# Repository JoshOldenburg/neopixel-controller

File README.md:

Neopixel Controllers
====================

Various Neopixel-style LED strip controllers based on the ATtiny85 microcontroller. Due to their size these aren't capable of more than 1A or so, preferably much less. The `neopixel-controller` files are for a standalone controller board.

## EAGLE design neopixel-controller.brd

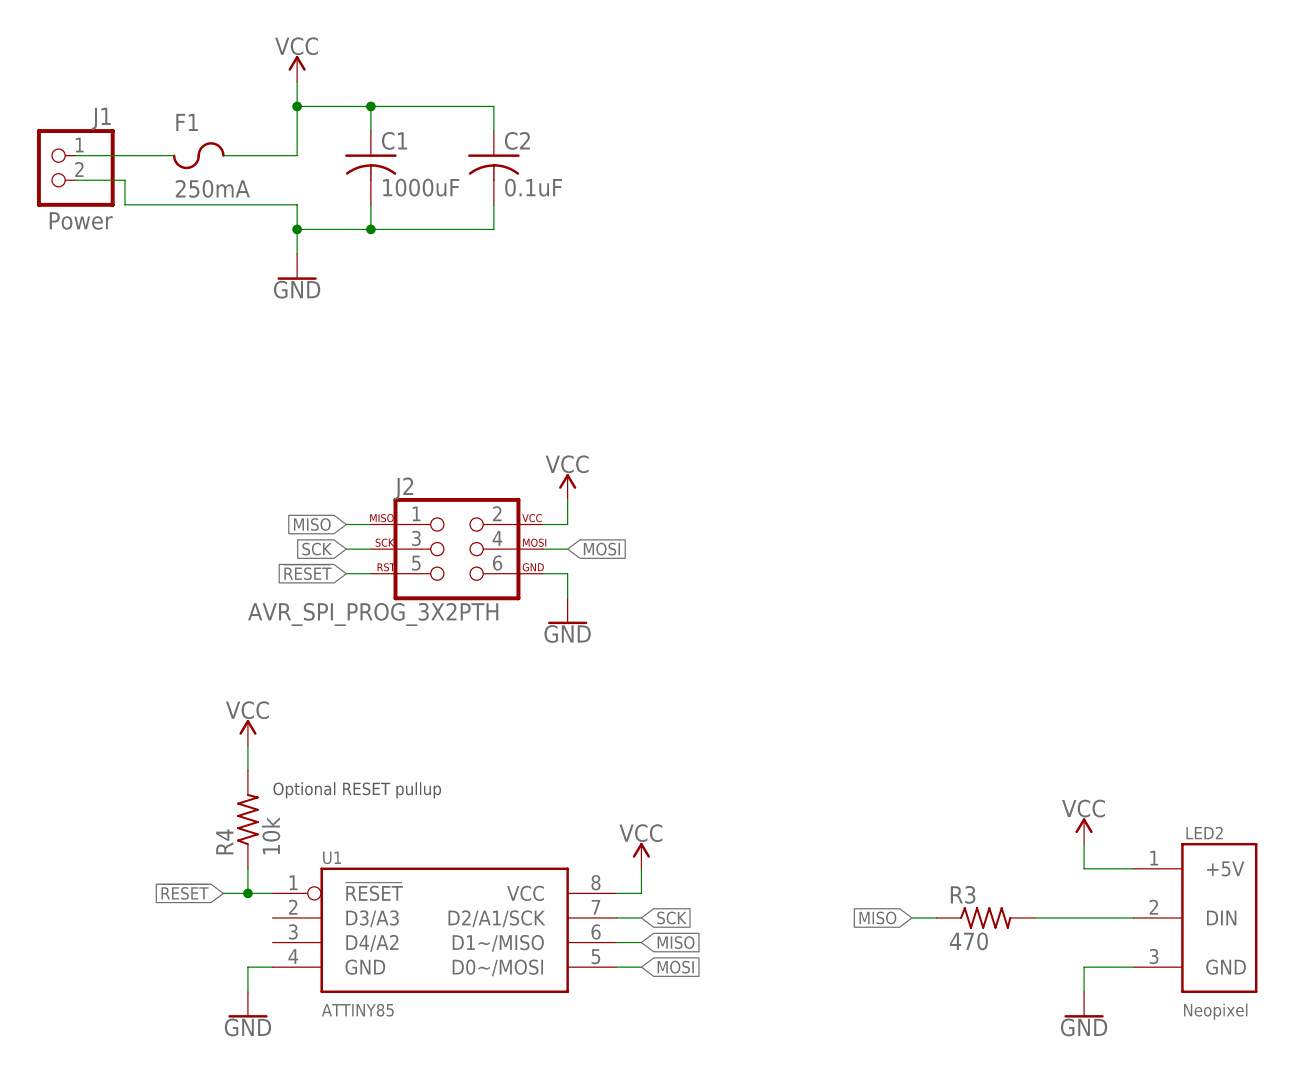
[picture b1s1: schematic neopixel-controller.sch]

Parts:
C1: 1000uF; CAP-3,5-8
C2: 0.1uF; C0805
F1: 250mA; F1206
J1: Power; 1X02
J2: AVR_SPI_PROG_3X2PTH; 2X3
LED2: Neopixel; NEOPIXEL_PINHEAD
R3: 470; R0805
R4: 10k; R0805
U1: ATTINY85; 8S2

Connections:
!RESET!: J2.5, R4.1, U1.1 (!RESET!)
GND: C1.NEGATIVE, C2.2, J1.2, J2.6, LED2.3 (GND), U1.4 (GND)
MISO: J2.1, R3.1, U1.6 (D1~/MISO)
MOSI: J2.4, U1.5 (D0~/MOSI)
unnamed: LED2.2 (DIN), R3.2
unnamed: F1.1, J1.1
SCK: J2.3, U1.7 (D2/A1/SCK)
VCC: C1.POSITIVE, C2.1, F1.2, J2.2, LED2.1 (+5V), R4.2, U1.8 (VCC)

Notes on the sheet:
Optional RESET pullup

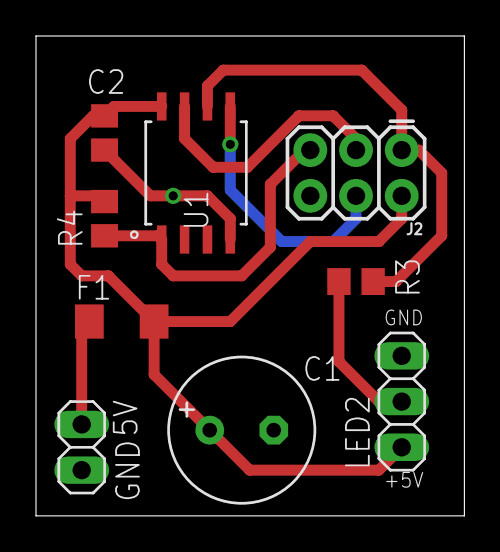
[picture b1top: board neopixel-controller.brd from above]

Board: 2 copper layers, 23.8 x 26.7 mm, 10 parts (1 on the bottom side), 8 nets.

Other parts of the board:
U$1: ROBOBUZZ_0.4X

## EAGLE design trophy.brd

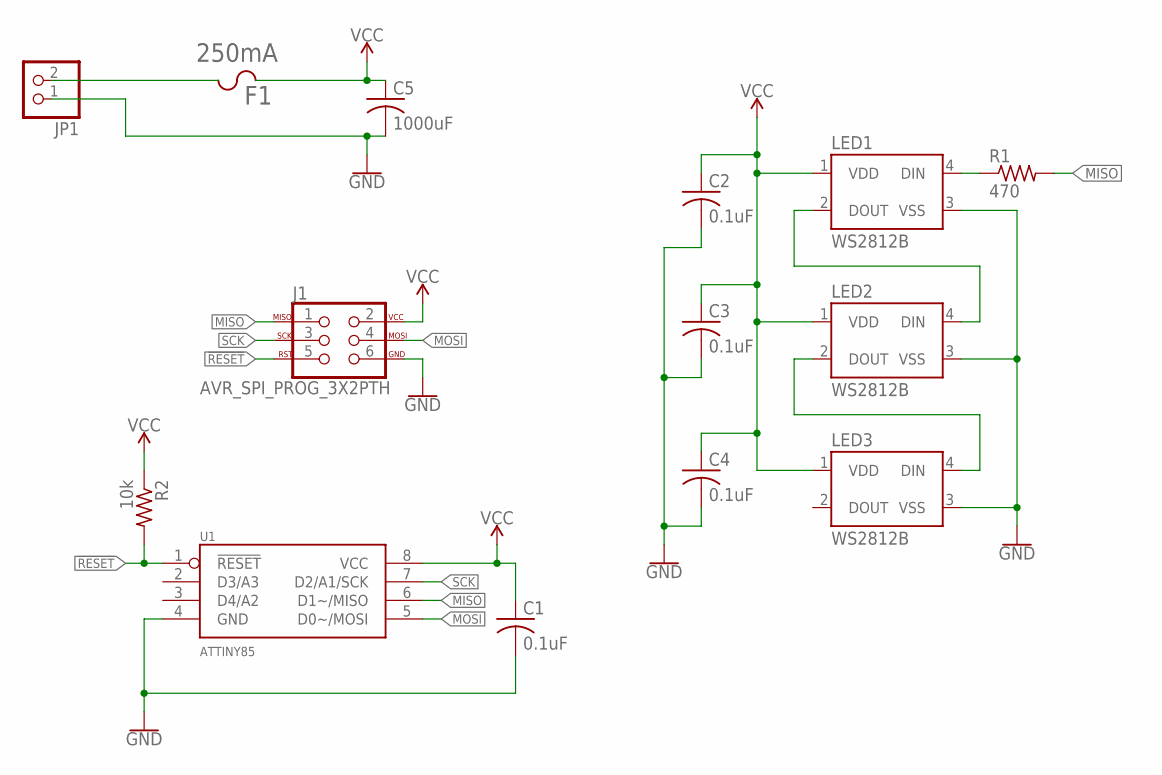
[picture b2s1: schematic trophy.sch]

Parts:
C1, C2, C3, C4: 0.1uF; C0805
C5: 1000uF; CAP-3,5-8
F1: 250mA; F1206
J1: AVR_SPI_PROG_3X2PTH; 2X3
JP1: PINHD-1X2; 1X02
LED1, LED2, LED3: WS2812B; 5050
R1: 470; R0805
R2: 10k; R0805
U1: ATTINY85; 8S2

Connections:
!RESET!: J1.5, R2.2, U1.1 (!RESET!)
GND: C1.2, C2.2, C3.2, C4.2, C5.NEGATIVE, J1.6, JP1.1, LED1.3 (VSS), LED2.3 (VSS), LED3.3 (VSS), U1.4 (GND)
MISO: J1.1, R1.2, U1.6 (D1~/MISO)
MOSI: J1.4, U1.5 (D0~/MOSI)
unnamed: LED1.2 (DOUT), LED2.4 (DIN)
unnamed: LED2.2 (DOUT), LED3.4 (DIN)
unnamed: F1.2, JP1.2
unnamed: LED1.4 (DIN), R1.1
SCK: J1.3, U1.7 (D2/A1/SCK)
VCC: C1.1, C2.1, C3.1, C4.1, C5.POSITIVE, F1.1, J1.2, LED1.1 (VDD), LED2.1 (VDD), LED3.1 (VDD), R2.1, U1.8 (VCC)

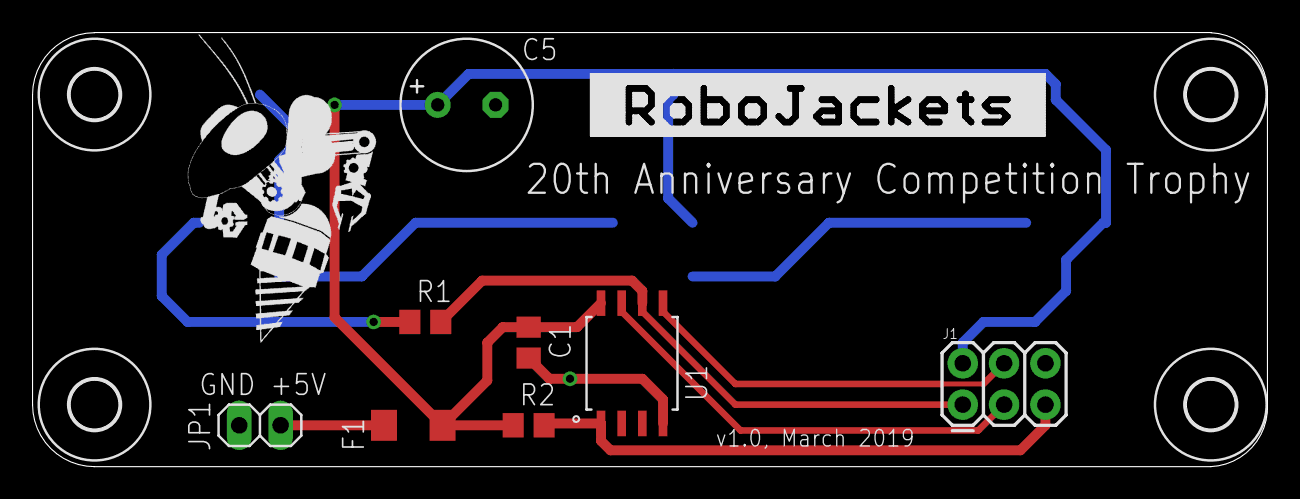
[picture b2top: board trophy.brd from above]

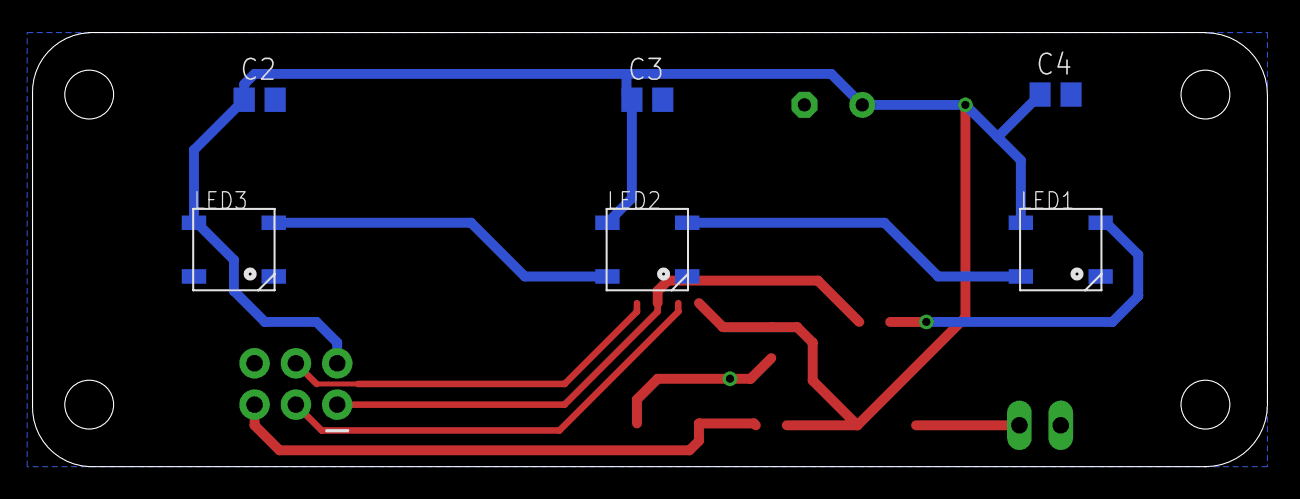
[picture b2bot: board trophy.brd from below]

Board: 2 copper layers, 75.9 x 26.7 mm, 20 parts (6 on the bottom side), 10 nets.

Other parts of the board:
U$1, U$2, U$3, U$4: 3,0
U$5: ROBOBUZZ_1.0X
U$6: ROBOJACKETS

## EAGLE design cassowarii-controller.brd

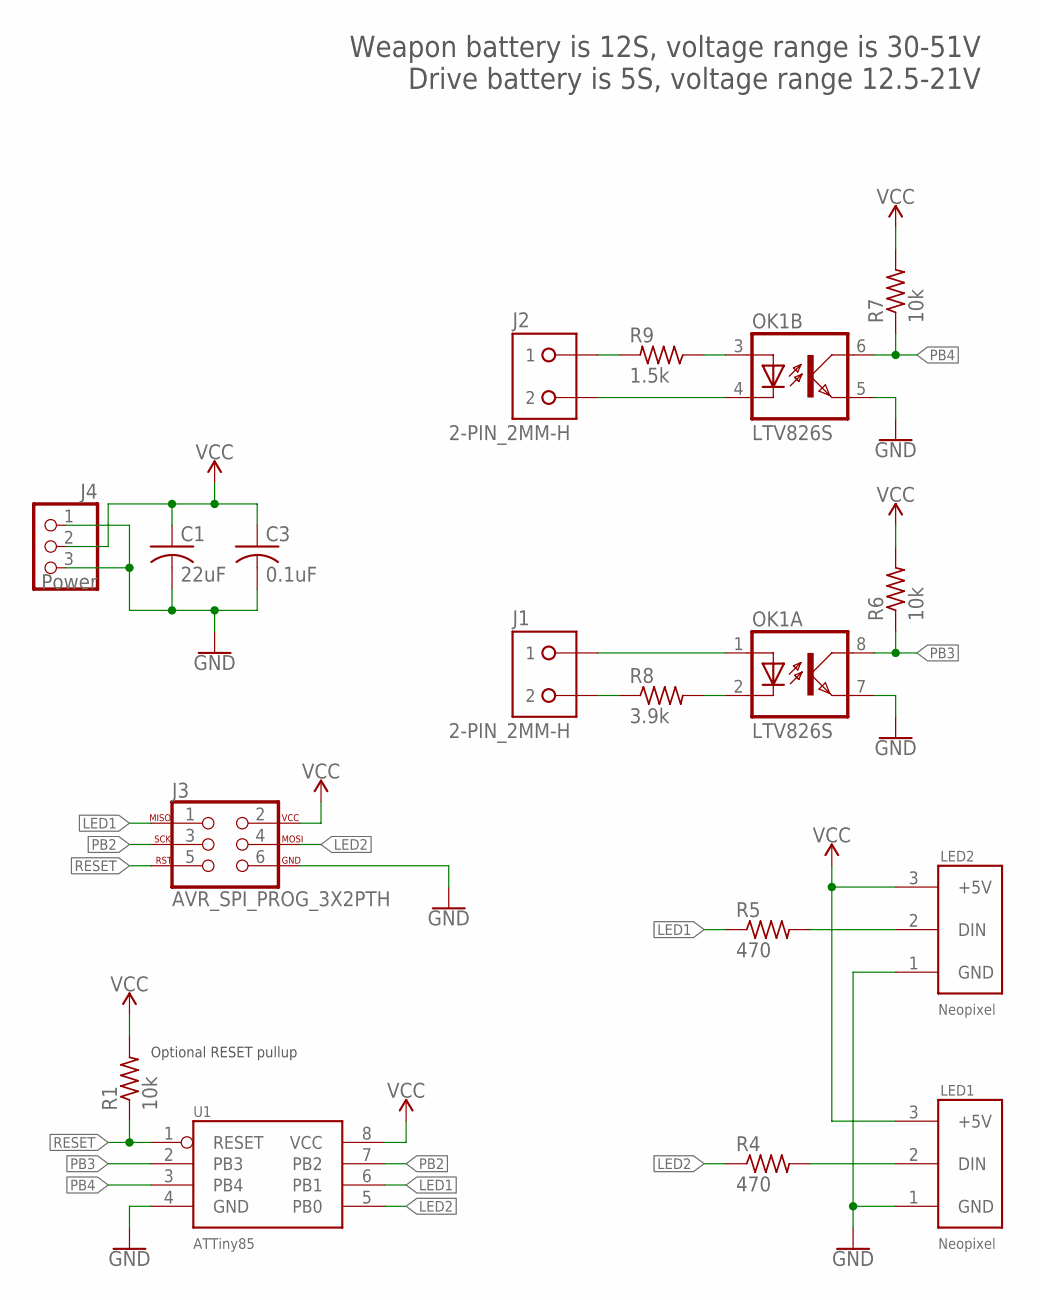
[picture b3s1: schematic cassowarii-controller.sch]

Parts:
C1: 22uF; C0805
C3: 0.1uF; C0805
J1, J2: 2-PIN_2MM-H; 2MM-2-H
J3: AVR_SPI_PROG_3X2PTH; 2X3
J4: Power; 1X03
LED1, LED2: Neopixel; 2MM-3-H
OK1: LTV826S; DIL8-SMD
R1, R6, R7: 10k; R0805
R4, R5: 470; R0805
R8: 3.9k; 0207/2V
R9: 1.5k; 0207/2V
U1: ATTiny85; SOIC8

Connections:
GND: C1.2, C3.2, J3.6, J4.1, J4.3, LED1.1 (GND), LED2.1 (GND), OK1.5 (EMIT), OK1.7 (EMIT), U1.4 (GND)
LED1: J3.1, R5.1, U1.6 (PB1)
LED2: J3.4, R4.1, U1.5 (PB0)
unnamed: LED1.2 (DIN), R4.2
unnamed: LED2.2 (DIN), R5.2
unnamed: J2.1, R9.2
unnamed: J1.2, R8.1
unnamed: OK1.3 (A), R9.1
unnamed: J2.2, OK1.4 (C)
unnamed: J1.1, OK1.1 (A)
unnamed: OK1.2 (C), R8.2
PB2: J3.3, U1.7 (PB2)
PB3: OK1.8 (COL), R6.1, U1.2 (PB3)
PB4: OK1.6 (COL), R7.1, U1.3 (PB4)
RESET: J3.5, R1.1, U1.1 (RESET)
VCC: C1.1, C3.1, J3.2, J4.2, LED1.3 (+5V), LED2.3 (+5V), R1.2, R6.2, R7.2, U1.8 (VCC)

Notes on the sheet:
Optional RESET pullup
Weapon battery is 12S, voltage range is 30-51V Drive battery is 5S, voltage range 12.5-21V

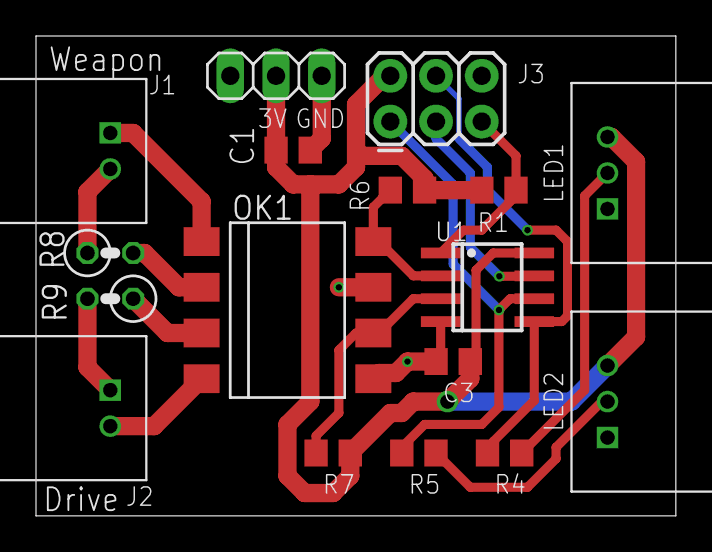
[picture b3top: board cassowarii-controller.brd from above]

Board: 2 copper layers, 35.5 x 26.7 mm, 18 parts (1 on the bottom side), 16 nets.

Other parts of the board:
U$1: ROBOBUZZ_0.6X

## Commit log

2018-12-04 Initial revision
2018-12-06 Switch to both planes being ground planes
2018-12-08 Final revision
2018-12-08 Add initial Cassowarii LED controller design
2018-12-08 Add schematic of what the original Cassowari LED controller was
2018-12-08 New version of Cassowarii controller with proper optoisolators
2019-01-08 Initial swap of Neopixel controller to SOIC ATTiny85
2019-01-09 Redesign Cassowarii controller to use SOIC ATTiny85
2019-01-09 Update schematic PDF
2019-01-09 Fix DRC errors
2019-01-09 Add readme
2019-01-09 Straighten bottom ground plane
2019-01-09 Add links to readme
2019-01-09 Fix spacing
2019-01-09 Add design review notes
2019-01-10 Add spots for through hole power resistors
2019-01-11 Remove regulator
2019-01-13 Update notes to reflect fixes
2019-01-13 Replace optoisolator
2019-01-14 Remove Cassowari files
    They have been moved to a separate repository
2019-02-25 Initial redesign for production run 2
2019-02-25 Revert neopixel-controller to neopixel-v1.0 and remove unnecessary things for 20th anniversary trophy production
2019-03-04 Add initial trophy controller
2019-03-04 Move caps to give more clearance for acrylic holder
2019-03-04 Bump via size
2019-03-05 Round corners and make final tweaks for trophy
2019-03-05 Reroute original controller to use a SOIC ATtiny85

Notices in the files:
parts and their libraries:
SparkFun-Connectors: Licensing: Creative Commons ShareAlike 4.0 International - https://creativecommons.org/licenses/by-sa/4.0
